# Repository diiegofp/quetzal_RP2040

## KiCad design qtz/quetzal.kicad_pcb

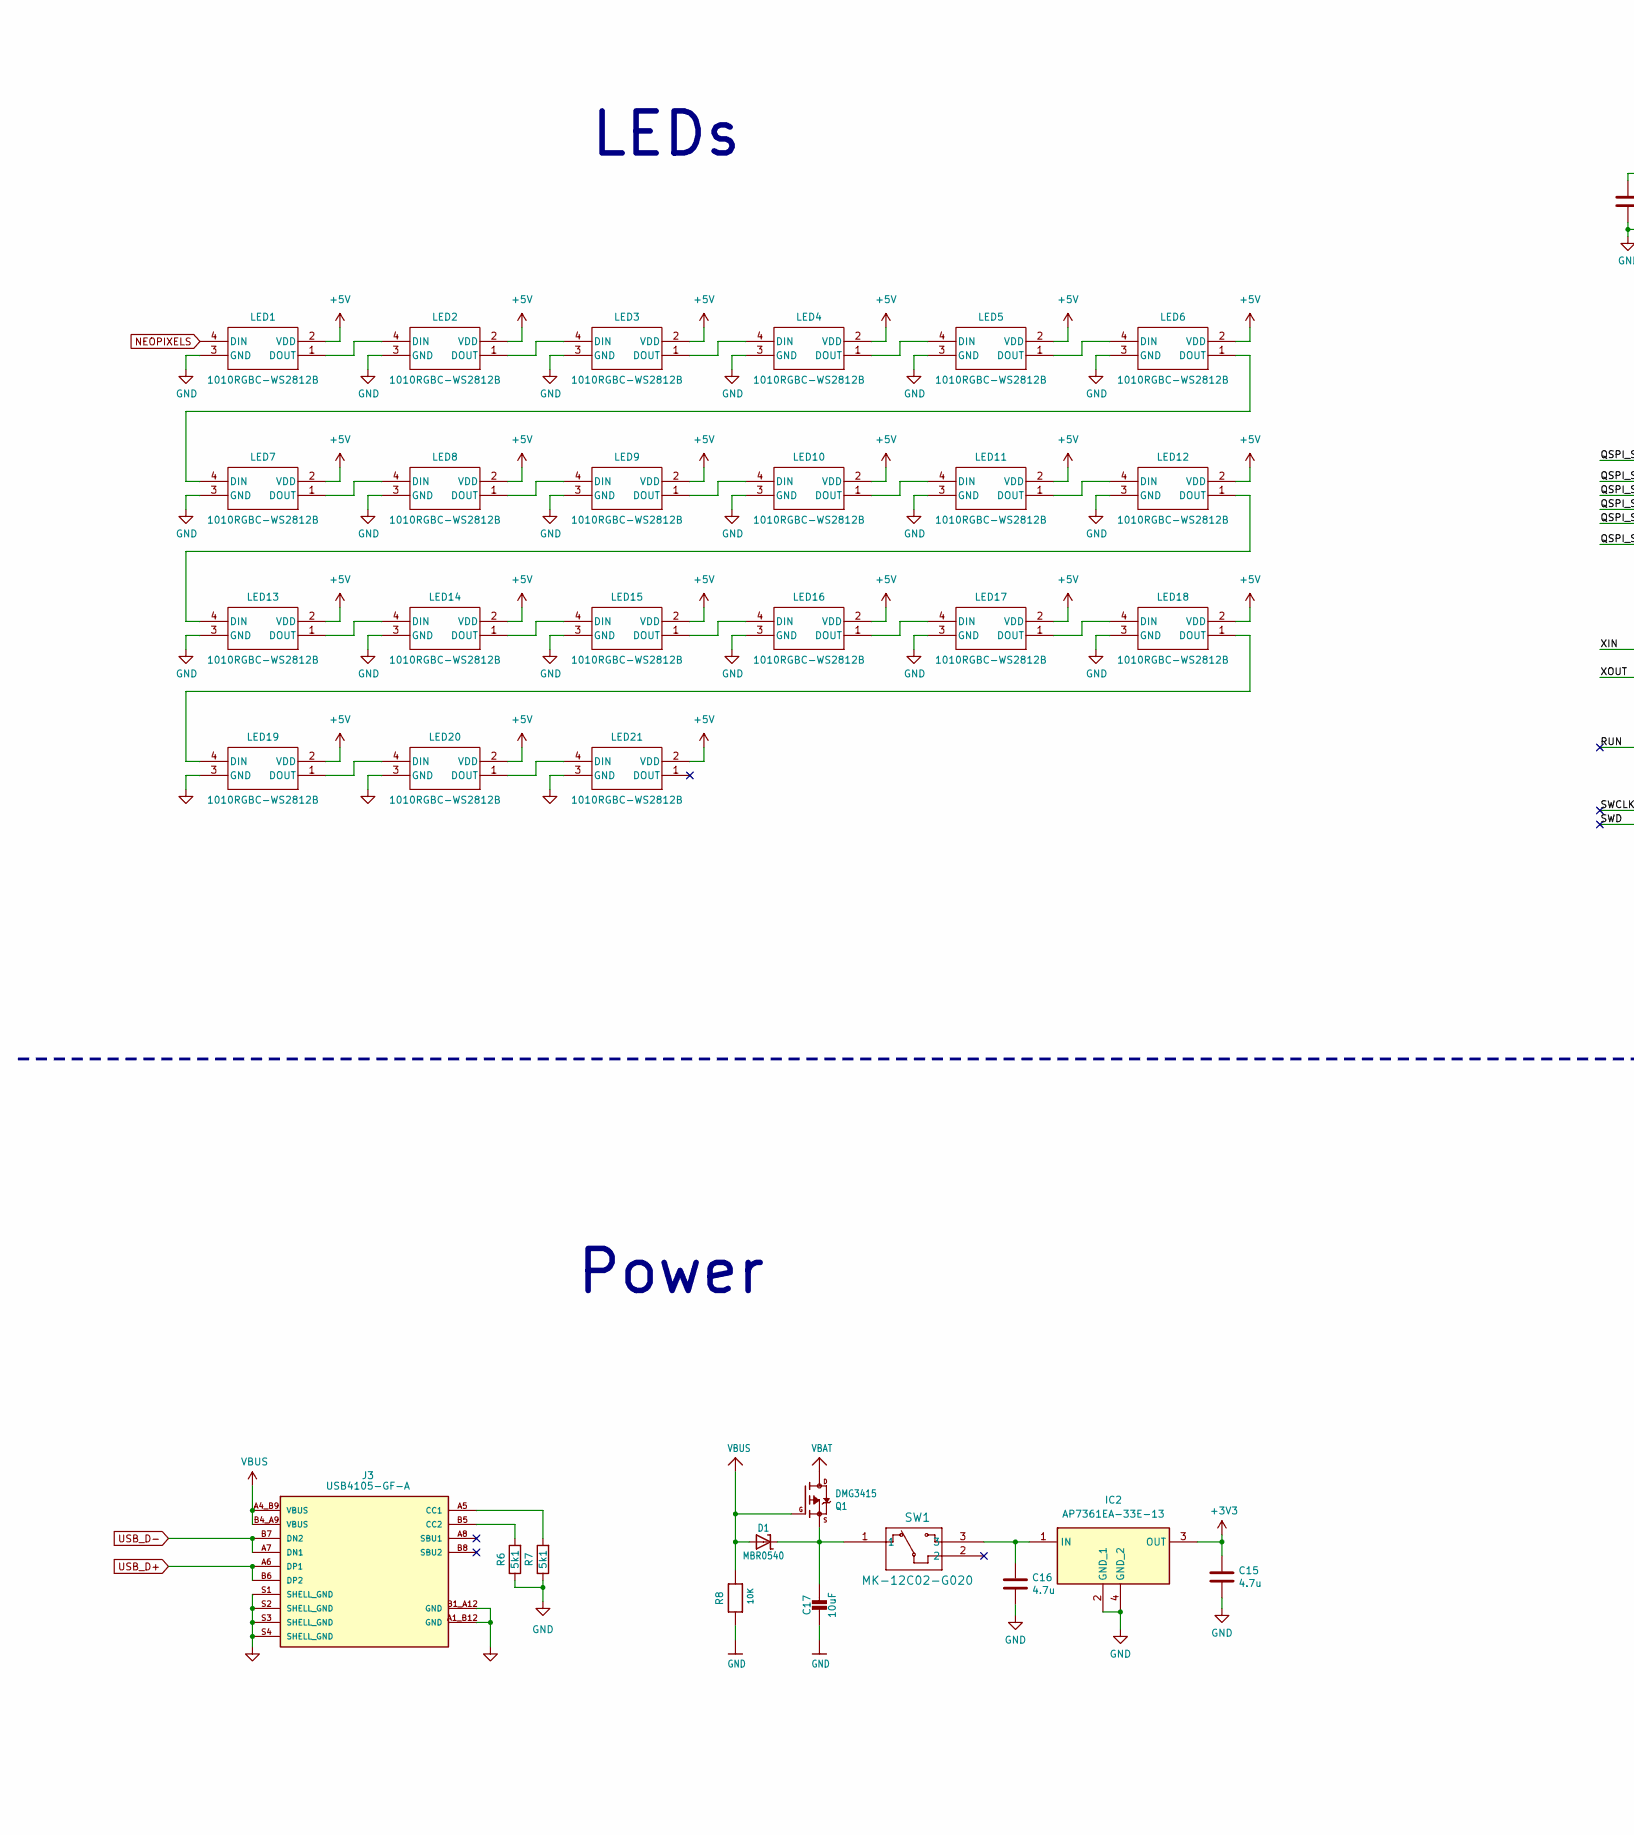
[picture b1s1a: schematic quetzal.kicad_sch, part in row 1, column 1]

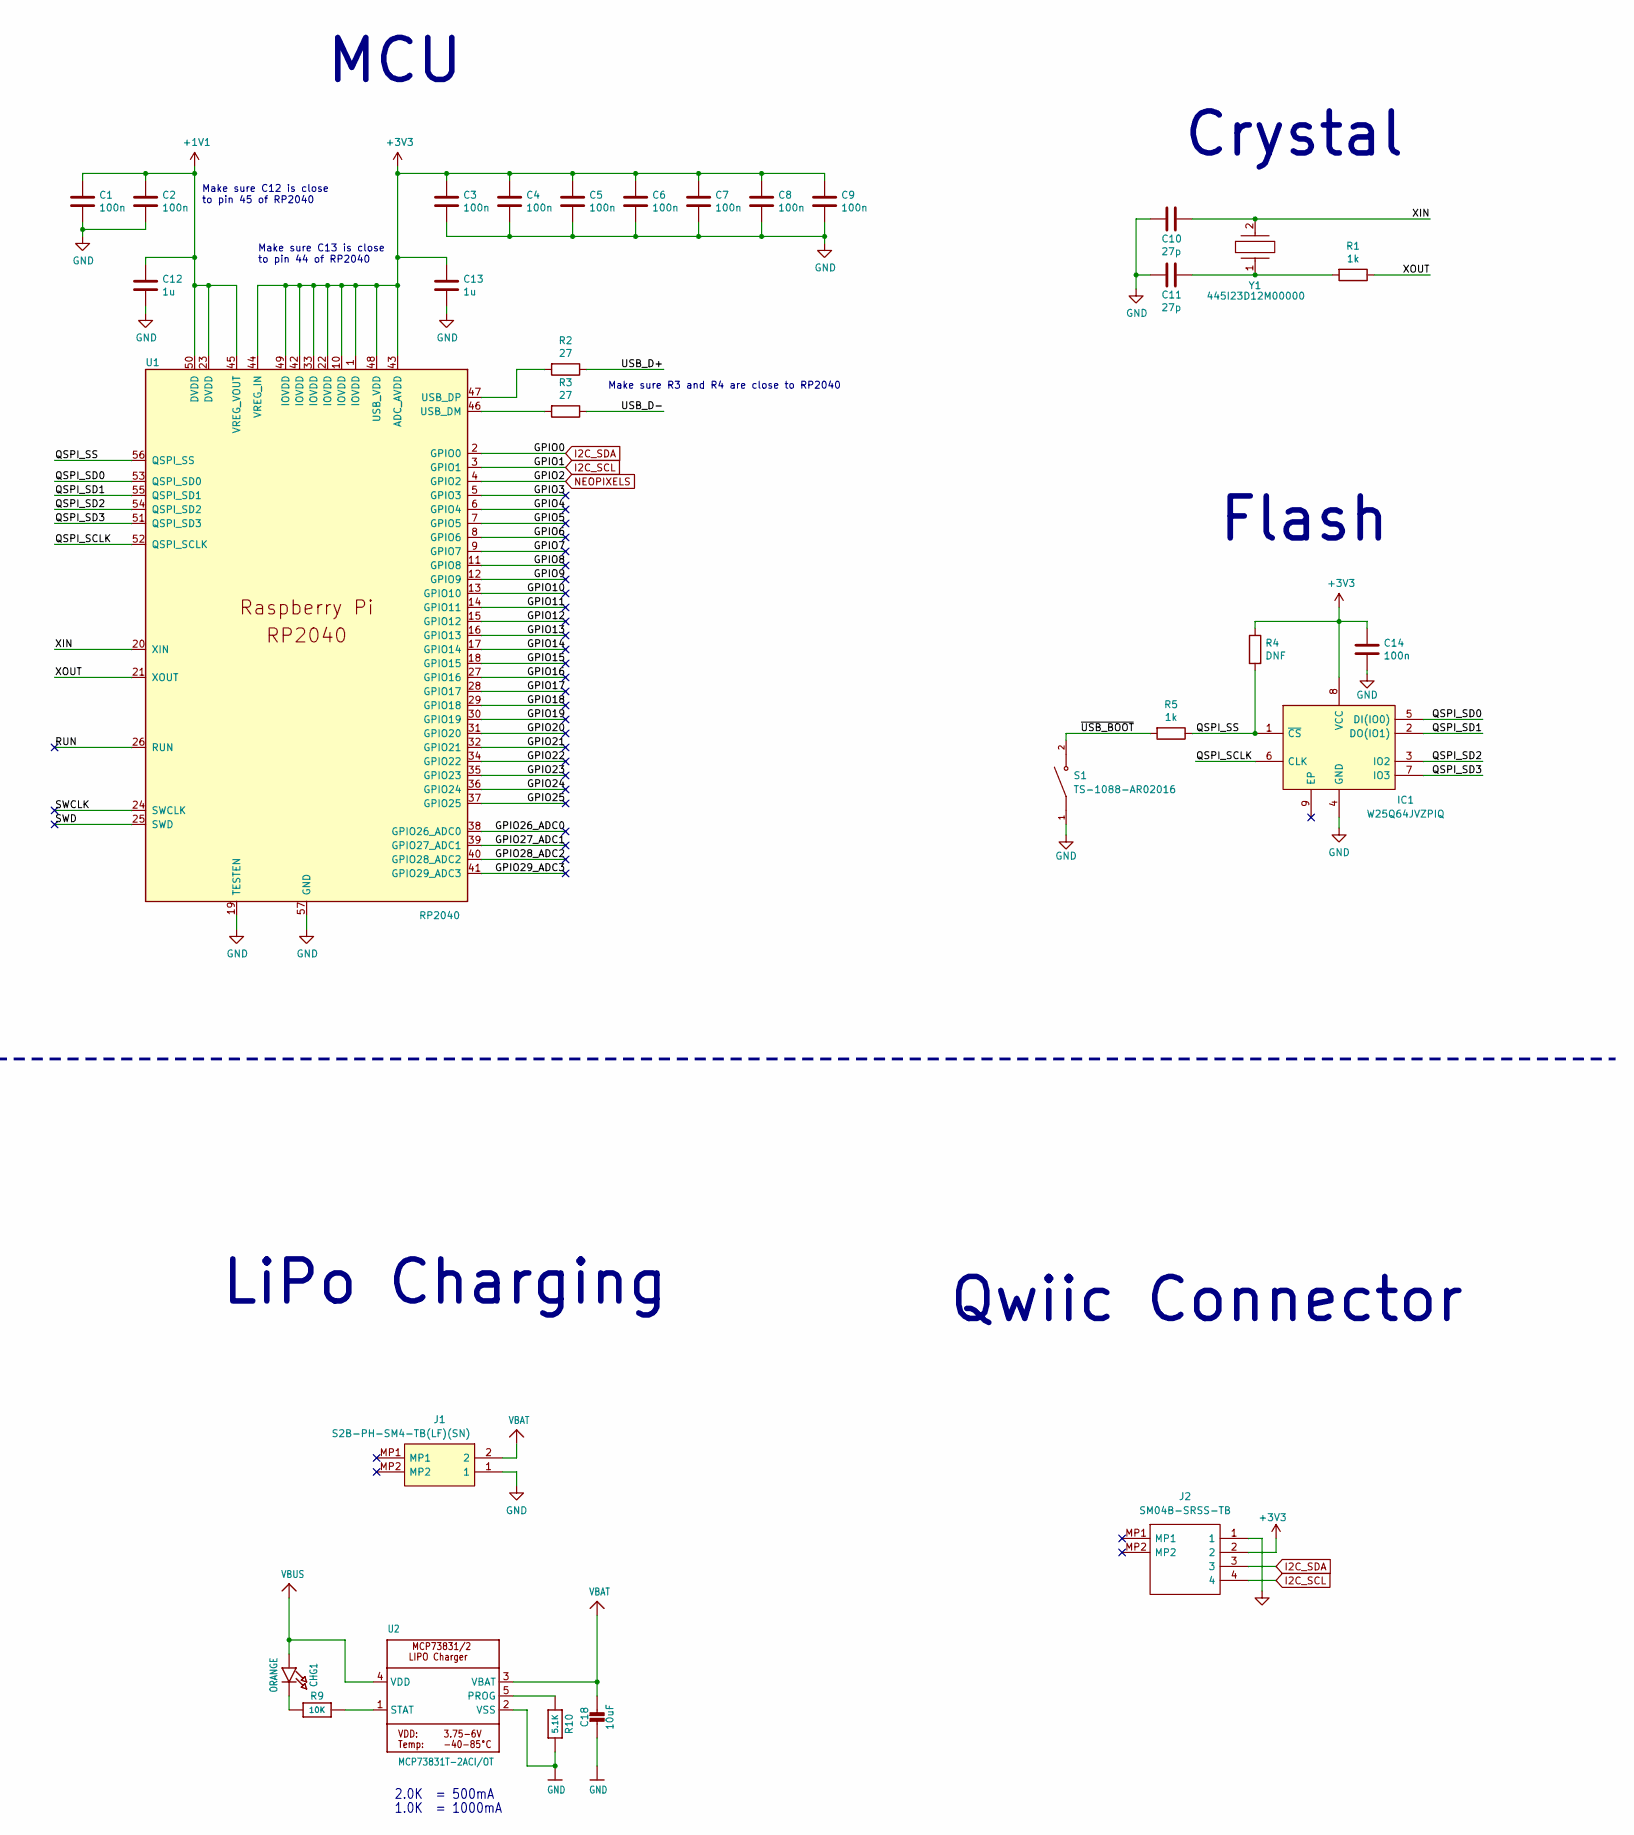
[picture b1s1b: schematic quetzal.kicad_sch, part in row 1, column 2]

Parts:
C1, C2, C3, C4, C5, C6, C7, C8, C9, C14: 100n; C_0402_1005Metric
C10, C11: 27p; C_0402_1005Metric
C12, C13: 1u; C_0402_1005Metric
C15, C16: 4.7u; C_0603_1608Metric
C17, C18: 10uF; C_0805_2012Metric
CHG1: ORANGE; LED_0402_1005Metric
D1: MBR0540; D_SOD-123
IC1: W25Q64JVZPIQ; SON80P400X400X50-9N; Mouser Part Number 454-W25Q128JVPIM
IC2: AP7361EA-33E-13; SOT230P700X180-4N; Mouser Part Number 621-AP7361EA-33E-13
J1: S2B-PH-SM4-TB(LF)(SN); JST_PH_S2B-PH-SM4-TB_1x02-1MP_P2.00mm_Horizontal; Mouser Part Number 538-53261-0271
J2: SM04B-SRSS-TB; SM04BSRSSTB; Manufacturer_Part_Number SM04B-SRSS-TB
J3: USB4105-GF-A; GCT_USB4105-GF-A; PARTREV A3
LED1, LED2, LED3, LED4, LED5, LED6, LED7, LED8, LED9, LED10, LED11, LED12, LED13, LED14, LED15, LED16, LED17, LED18, LED19, LED20, LED21: 1010RGBC-WS2812B; SMD4_XL-1010RGBC_XLG
Q1: DMG3415; SOT-23
R1, R5: 1k; R_0402_1005Metric
R2, R3: 27; R_0402_1005Metric
R4: DNF; R_0402_1005Metric
R6, R7: 5k1; R_0201_0603Metric; Part No AF0201FR-075K1L
R8, R9: 10K; R_0402_1005Metric
R10: 5.1K; R_0402_1005Metric
S1: TS-1088-AR02016; SW_TS-1088-AR02016; PARTREV N/A
SW1: MK-12C02-G020; MK-12C02-G020_GSW
U1: RP2040; RP2040-QFN-56
U2: MCP73831T-2ACI/OT; SOT95P270X145-5N
Y1: 445I23D12M00000; 445I23D24M00000; Mouser Part Number 774-445I23D12M00000

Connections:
I2C_SCL: J2.4, U1.3 (GPIO1)
I2C_SDA: J2.3, U1.2 (GPIO0)
+1V1: C1.1, C2.1, C12.1, U1.23 (DVDD), U1.45 (VREG_VOUT), U1.50 (DVDD)
+3V3: C3.1, C4.1, C5.1, C6.1, C7.1, C8.1, C9.1, C13.1, C14.1, C15.1, IC1.8 (VCC), IC2.3 (OUT), J2.2, R4.1, U1.1 (IOVDD), U1.10 (IOVDD), U1.22 (IOVDD), U1.33 (IOVDD), U1.42 (IOVDD), U1.43 (ADC_AVDD), U1.44 (VREG_IN), U1.48 (USB_VDD), U1.49 (IOVDD); also elsewhere on the board
+5V: LED1.2 (VDD), LED2.2 (VDD), LED3.2 (VDD), LED4.2 (VDD), LED5.2 (VDD), LED6.2 (VDD), LED7.2 (VDD), LED8.2 (VDD), LED9.2 (VDD), LED10.2 (VDD), LED11.2 (VDD), LED12.2 (VDD), LED13.2 (VDD), LED14.2 (VDD), LED15.2 (VDD), LED16.2 (VDD), LED17.2 (VDD), LED18.2 (VDD), LED19.2 (VDD), LED20.2 (VDD), LED21.2 (VDD)
/GPIO3: U1.5 (GPIO3)
/GPIO4: U1.6 (GPIO4)
/GPIO5: U1.7 (GPIO5)
/GPIO6: U1.8 (GPIO6)
/GPIO7: U1.9 (GPIO7)
/GPIO8: U1.11 (GPIO8)
/GPIO9: U1.12 (GPIO9)
/GPIO10: U1.13 (GPIO10)
/GPIO11: U1.14 (GPIO11)
/GPIO12: U1.15 (GPIO12)
/GPIO13: U1.16 (GPIO13)
/GPIO14: U1.17 (GPIO14)
/GPIO15: U1.18 (GPIO15)
/GPIO16: U1.27 (GPIO16)
/GPIO17: U1.28 (GPIO17)
/GPIO18: U1.29 (GPIO18)
/GPIO19: U1.30 (GPIO19)
/GPIO20: U1.31 (GPIO20)
/GPIO21: U1.32 (GPIO21)
/GPIO22: U1.34 (GPIO22)
/GPIO23: U1.35 (GPIO23)
/GPIO24: U1.36 (GPIO24)
/GPIO25: U1.37 (GPIO25)
/GPIO26_ADC0: U1.38 (GPIO26_ADC0)
/GPIO27_ADC1: U1.39 (GPIO27_ADC1)
/GPIO28_ADC2: U1.40 (GPIO28_ADC2)
/GPIO29_ADC3: U1.41 (GPIO29_ADC3)
/QSPI_SCLK: IC1.6 (CLK), U1.52 (QSPI_SCLK)
/QSPI_SD0: IC1.5 (DI(IO0)), U1.53 (QSPI_SD0)
/QSPI_SD1: IC1.2 (DO(IO1)), U1.55 (QSPI_SD1)
/QSPI_SD2: IC1.3 (IO2), U1.54 (QSPI_SD2)
/QSPI_SD3: IC1.7 (IO3), U1.51 (QSPI_SD3)
/QSPI_SS: IC1.1 (~CS), R4.2, R5.1, U1.56 (QSPI_SS)
/RUN: U1.26 (RUN)
/SWCLK: U1.24 (SWCLK)
/SWD: U1.25 (SWD)
/XIN: C10.1, U1.20 (XIN), Y1.2
/XOUT: R1.1, U1.21 (XOUT)
/~USB_BOOT: R5.2, S1.2
GND: C1.2, C2.2, C3.2, C4.2, C5.2, C6.2, C7.2, C8.2, C9.2, C10.2, C11.2, C12.2, C13.2, C14.2, C15.2, C16.2, C17.2, C18.2, IC1.4 (GND), IC2.2 (GND_1), IC2.4 (GND_2), J1.1, J2.1, J3.A1_B12 (GND), J3.B1_A12 (GND), J3.S1 (SHELL_GND), J3.S2 (SHELL_GND), J3.S3 (SHELL_GND), J3.S4 (SHELL_GND), LED1.3 (GND), LED2.3 (GND), LED3.3 (GND), LED4.3 (GND), LED5.3 (GND), LED6.3 (GND), LED7.3 (GND), LED8.3 (GND), LED9.3 (GND), LED10.3 (GND), LED11.3 (GND), LED12.3 (GND), LED13.3 (GND), LED14.3 (GND), LED15.3 (GND), LED16.3 (GND), LED17.3 (GND), LED18.3 (GND), LED19.3 (GND), LED20.3 (GND), LED21.3 (GND), R6.1, R7.1, R8.1, R10.2, S1.1, U1.19 (TESTEN), U1.57 (GND), U2.2 (VSS); also elsewhere on the board
NEOPIXELS: LED1.4 (DIN), U1.4 (GPIO2)
unnamed: C11.1, R1.2, Y1.1
unnamed: CHG1.1 (C), R9.1
unnamed: C17.1, D1.1 (C), Q1.2 (S), SW1.1
unnamed: C16.1, IC2.1 (IN), SW1.3
unnamed: J3.A5 (CC1), R7.2
unnamed: J3.B5 (CC2), R6.2
unnamed: LED1.1 (DOUT), LED2.4 (DIN)
unnamed: LED2.1 (DOUT), LED3.4 (DIN)
unnamed: LED3.1 (DOUT), LED4.4 (DIN)
unnamed: LED4.1 (DOUT), LED5.4 (DIN)
unnamed: LED5.1 (DOUT), LED6.4 (DIN)
unnamed: LED6.1 (DOUT), LED7.4 (DIN)
unnamed: LED7.1 (DOUT), LED8.4 (DIN)
unnamed: LED8.1 (DOUT), LED9.4 (DIN)
unnamed: LED9.1 (DOUT), LED10.4 (DIN)
unnamed: LED10.1 (DOUT), LED11.4 (DIN)
unnamed: LED11.1 (DOUT), LED12.4 (DIN)
unnamed: LED12.1 (DOUT), LED13.4 (DIN)
unnamed: LED13.1 (DOUT), LED14.4 (DIN)
unnamed: LED14.1 (DOUT), LED15.4 (DIN)
unnamed: LED15.1 (DOUT), LED16.4 (DIN)
unnamed: LED16.1 (DOUT), LED17.4 (DIN)
unnamed: LED17.1 (DOUT), LED18.4 (DIN)
unnamed: LED18.1 (DOUT), LED19.4 (DIN)
unnamed: LED19.1 (DOUT), LED20.4 (DIN)
unnamed: LED20.1 (DOUT), LED21.4 (DIN)
unnamed: R3.2, U1.46 (USB_DM)
unnamed: R2.2, U1.47 (USB_DP)
unnamed: R10.1, U2.5 (PROG)
unnamed: R9.2, U2.1 (STAT)
USB_D+: J3.A6 (DP1), J3.B6 (DP2), R2.1
USB_D-: J3.A7 (DN1), J3.B7 (DN2), R3.1
VBAT: C18.1, J1.2, Q1.3 (D), U2.3 (VBAT)
VBUS: CHG1.2 (A), D1.2 (A), J3.A4_B9 (VBUS), J3.B4_A9 (VBUS), Q1.1 (G), R8.2, U2.4 (VDD)

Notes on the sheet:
Make sure C13 is close to pin 44 of RP2040
Crystal
2.0K = 500mA
Qwiic Connector
LiPo Charging
Make sure C12 is close to pin 45 of RP2040
Power
Flash
Make sure R3 and R4 are close to RP2040
MCU
LEDs
1.0K = 1000mA

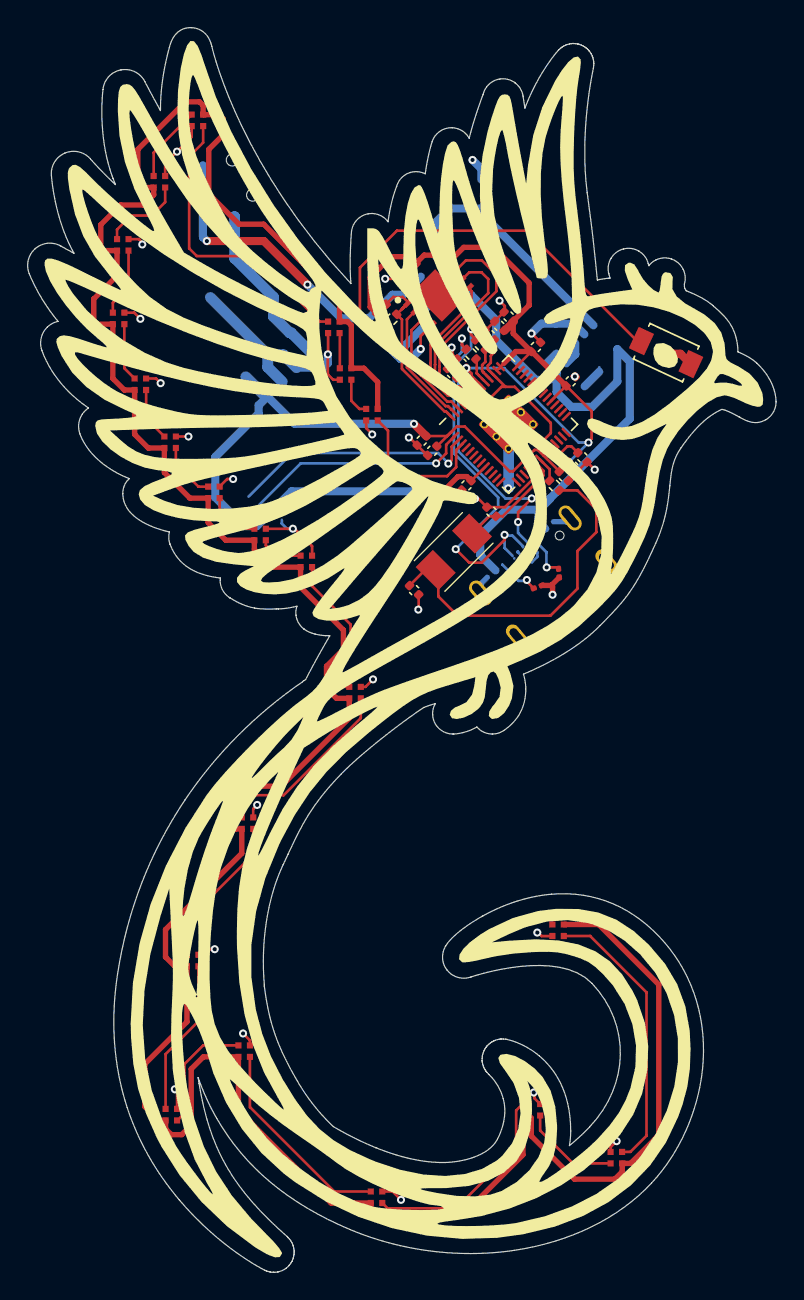
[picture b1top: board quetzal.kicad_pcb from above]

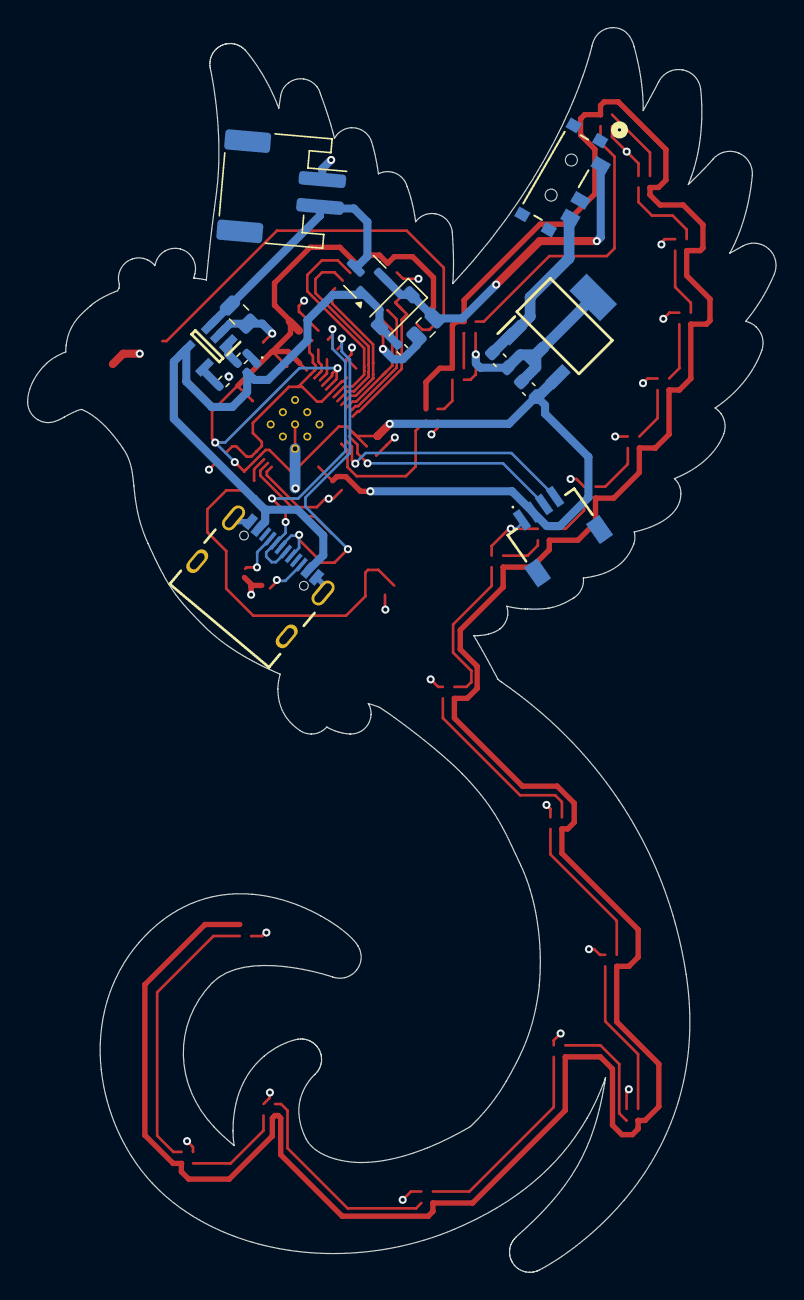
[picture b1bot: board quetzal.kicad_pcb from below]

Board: 4 copper layers, 55.4 x 92.1 mm, 64 parts (16 on the bottom side), 50 nets.

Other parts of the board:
C7#2, C9#2: 100n; C_0402_1005Metric

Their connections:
+3V3: C7#2.1, C9#2.1; also elsewhere on the board
GND: C7#2.2, C9#2.2; also elsewhere on the board

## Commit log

2025-08-19 Create a
